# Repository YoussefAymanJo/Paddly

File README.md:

# Paddly
## Description
Paddly is a customized macro pad that combines both customization and functionality. I actually made this to facilitate my daily use. It it consist of 6 switches with multiple functions, an OLED display for soup, customized 2 rotary encoders, and RGB LEDs. I was a beginner in 3D modeling, but I learned a lot from  Fusion tutorials.

## Why it was built
During my day, I use a laptop  almost all day. But while working on projects or designing on Canva, I struggle and tired alot to use multiplekeysy odoly some features, such as  copy manually and undo. So, built a macro pad that provides all the luxury in my usage. As it has 6 MX Cherry switches with customized functions.And 2 rotary encoders and a soup OLED display.

## How to use it / Build it
First, fabricate the PCB and solder the components. After that, set up the firmware on Pico, kmk firmware. Then test each key, OLED, encoders, and LEDs.after that print 
3d models. After that, assemble 3d  enclosure and setup heatinsert and m3 srews. Finally, test everything again.

## Schematic
I made a schematic in KiCad and used Scott Keebs' libraries for the MCU and OLED footprints.

## PCB
I routed the PCB and added the 3d models for components

## CAD
I used Fusion 360 for CAD, and this is my first time in the Fusion world. so i learned frommultiple YouTubee video s. Made a case, a plate, and a top cover. Also signed my name on the cover. I used the encoder's knob and DSA keycaps from the Hackpad Orpheus guide.

## Firmware
I used KMK firmware.

## BOM

## Zine

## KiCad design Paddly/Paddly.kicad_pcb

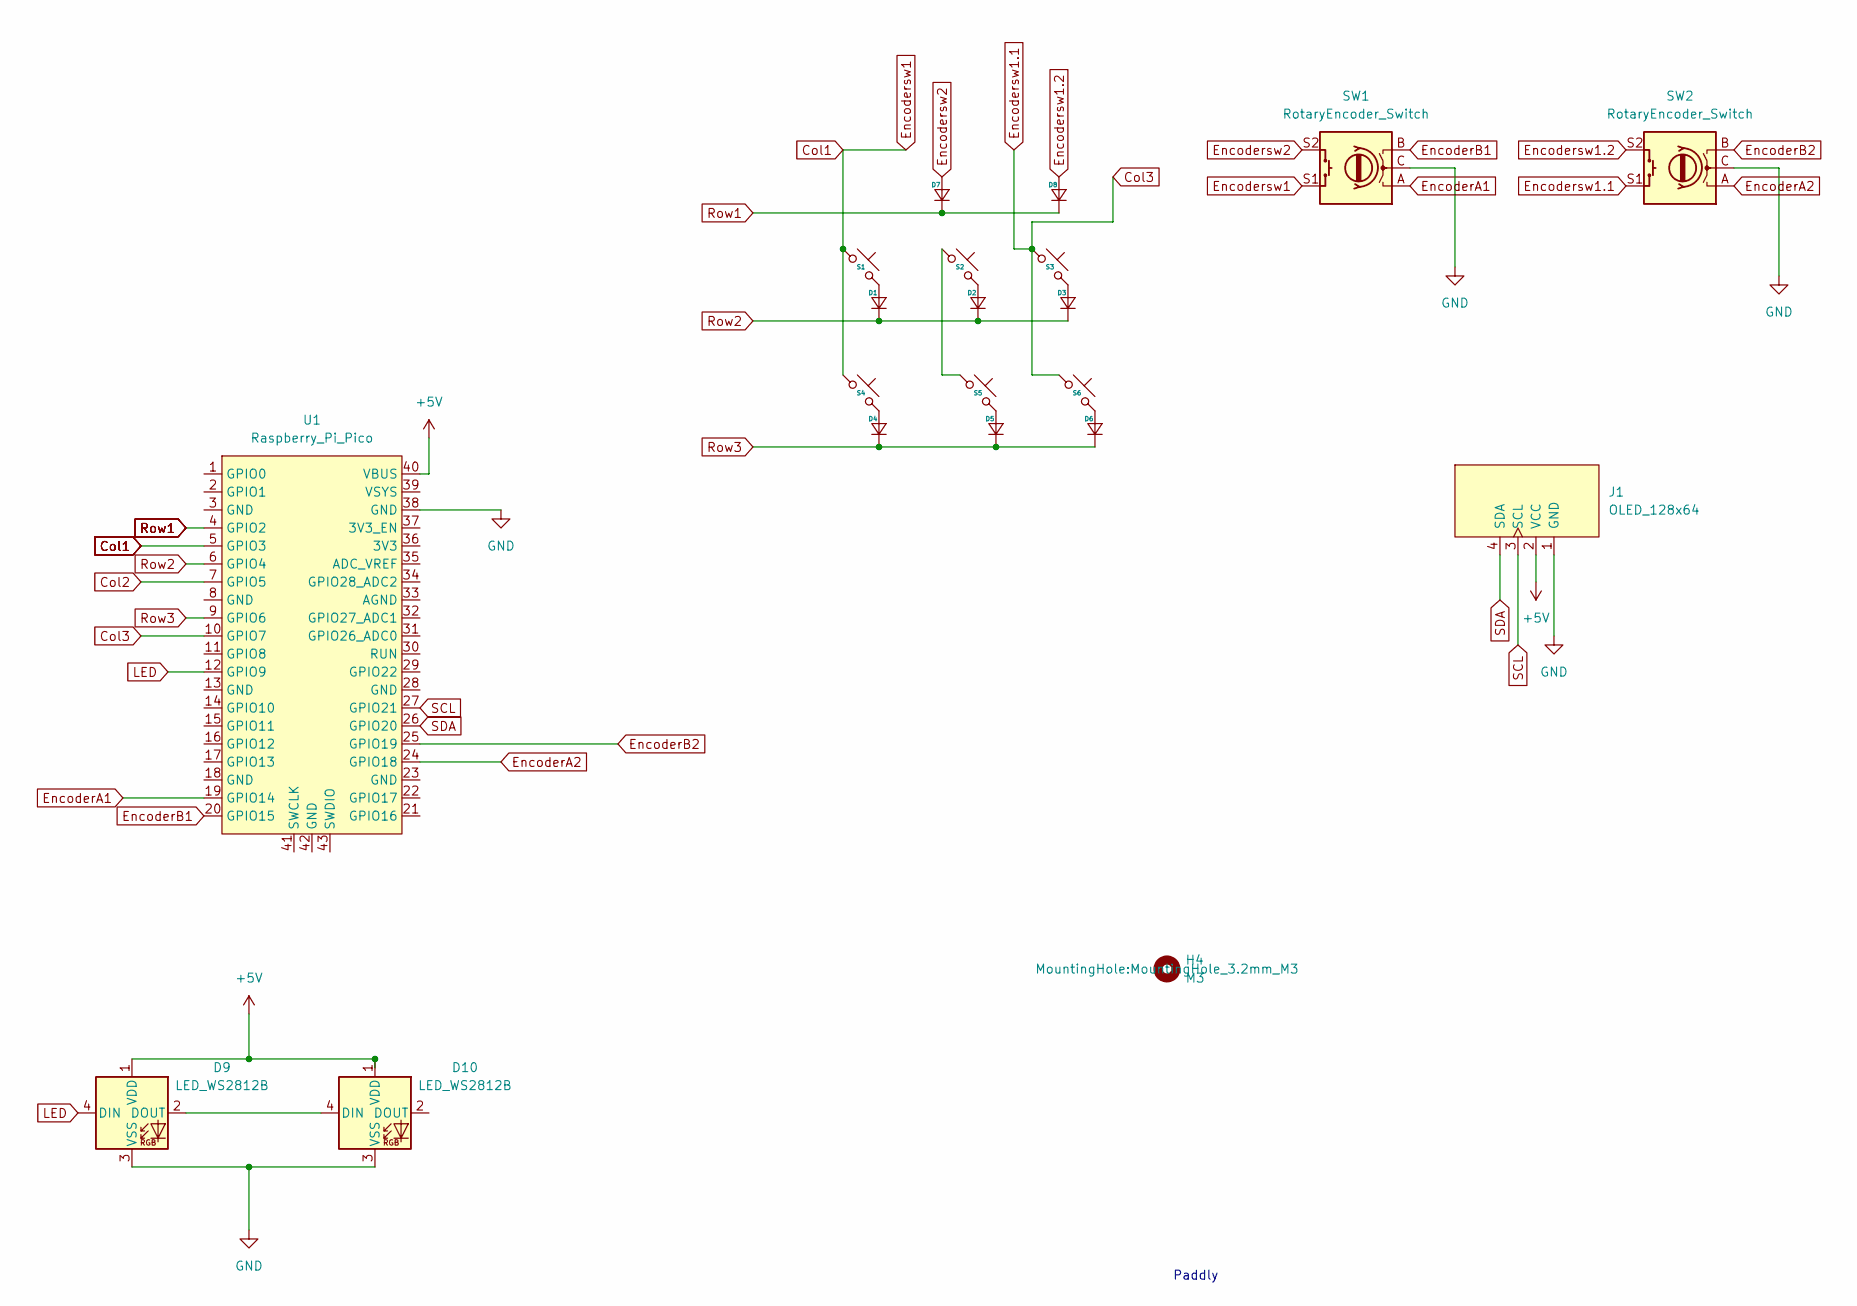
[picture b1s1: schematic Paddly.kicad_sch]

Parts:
D1, D2, D3, D4, D5, D6, D7, D8: Diode_DO-35
D9, D10: LED_WS2812B
H4: M3; MountingHole_3.2mm_M3
J1: OLED_128x64
S1, S2, S3, S4, S5, S6: MX_PCB_1.00u
SW1, SW2: RotaryEncoder_Switch; Encoder_EC11_MX
U1: Raspberry_Pi_Pico

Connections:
+5V: D9.1 (VDD), D10.1 (VDD), J1.2 (VCC), U1.40 (VBUS)
Col1: S1.1, S4.1, SW1.S1, U1.5 (GPIO3)
Col2: U1.7 (GPIO5)
Col3: S3.1, S6.1, SW2.S1, U1.10 (GPIO7)
EncoderA1: SW1.A, U1.19 (GPIO14)
EncoderA2: SW2.A, U1.24 (GPIO18)
EncoderB1: SW1.B, U1.20 (GPIO15)
EncoderB2: SW2.B, U1.25 (GPIO19)
Encodersw1.2: D8.2 (A), SW2.S2
Encodersw2: D7.2 (A), SW1.S2
GND: D9.3 (VSS), D10.3 (VSS), J1.1 (GND), SW1.C, SW2.C, U1.38 (GND)
LED: D9.4 (DIN), U1.12 (GPIO9)
unnamed: D1.2 (A), S1.2
unnamed: D2.2 (A), S2.2
unnamed: D3.2 (A), S3.2
unnamed: D4.2 (A), S4.2
unnamed: D5.2 (A), S5.2
unnamed: D6.2 (A), S6.2
unnamed: D9.2 (DOUT), D10.4 (DIN)
unnamed: S2.1, S5.1
Row1: D7.1 (K), D8.1 (K), U1.4 (GPIO2)
Row2: D1.1 (K), D2.1 (K), D3.1 (K), U1.6 (GPIO4)
Row3: D4.1 (K), D5.1 (K), D6.1 (K), U1.9 (GPIO6)
SCL: J1.3 (SCL), U1.27 (GPIO21)
SDA: J1.4 (SDA), U1.26 (GPIO20)

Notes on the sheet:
Paddly

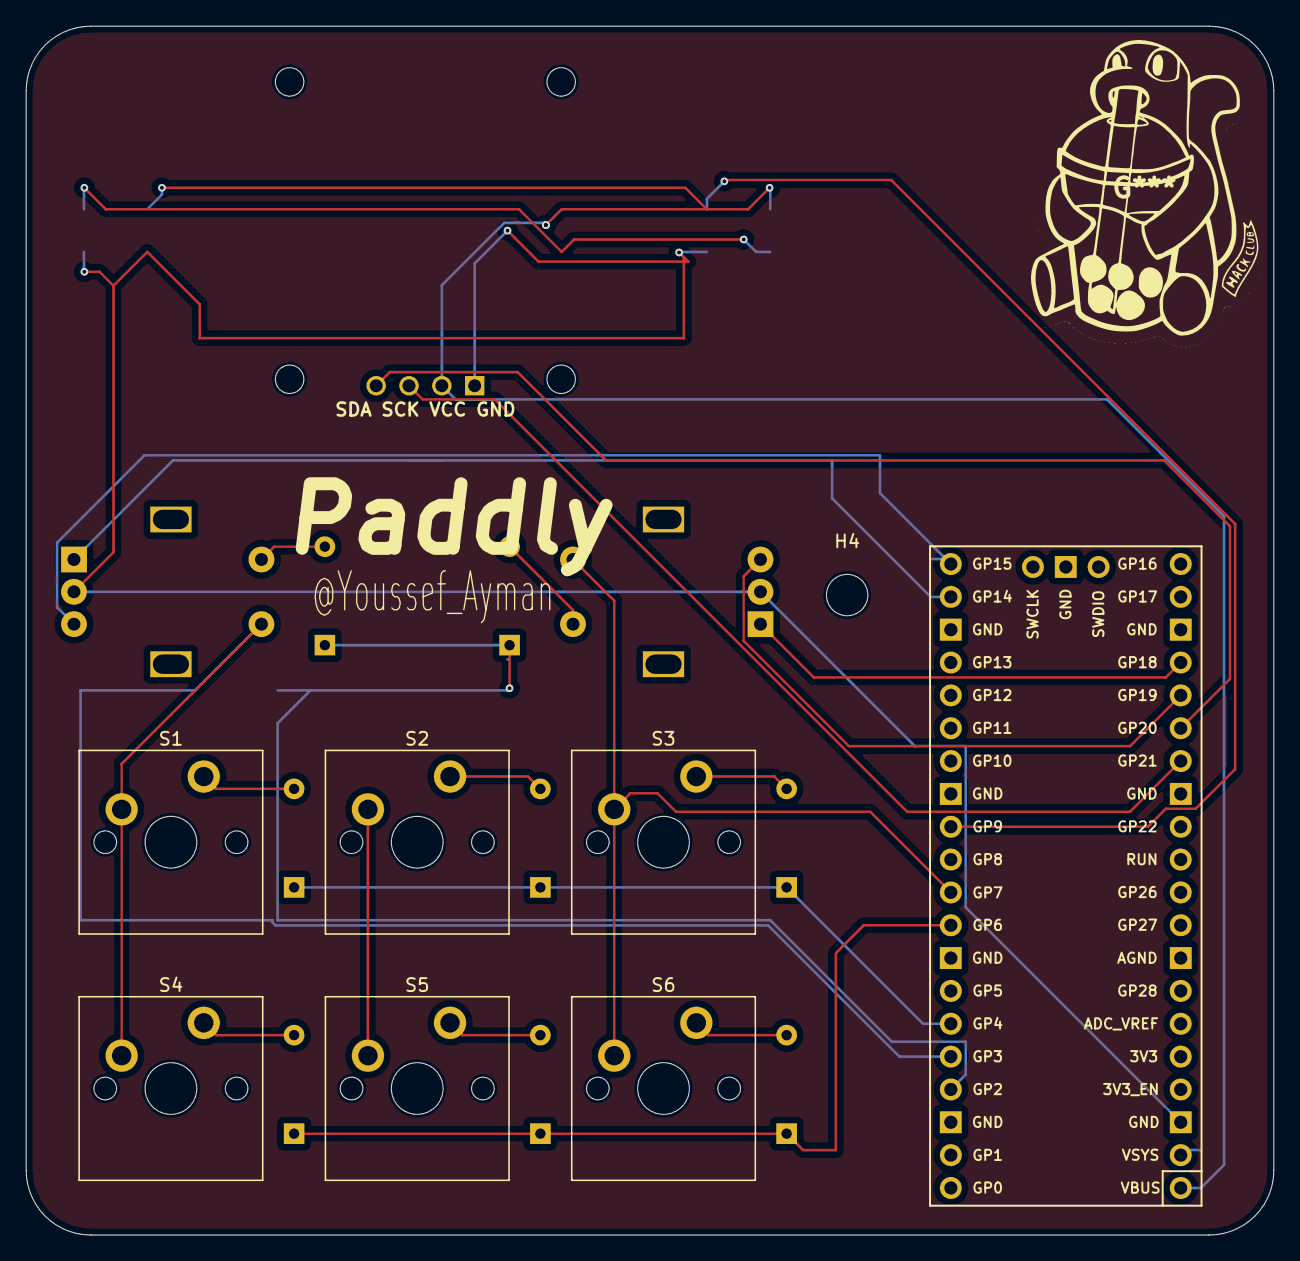
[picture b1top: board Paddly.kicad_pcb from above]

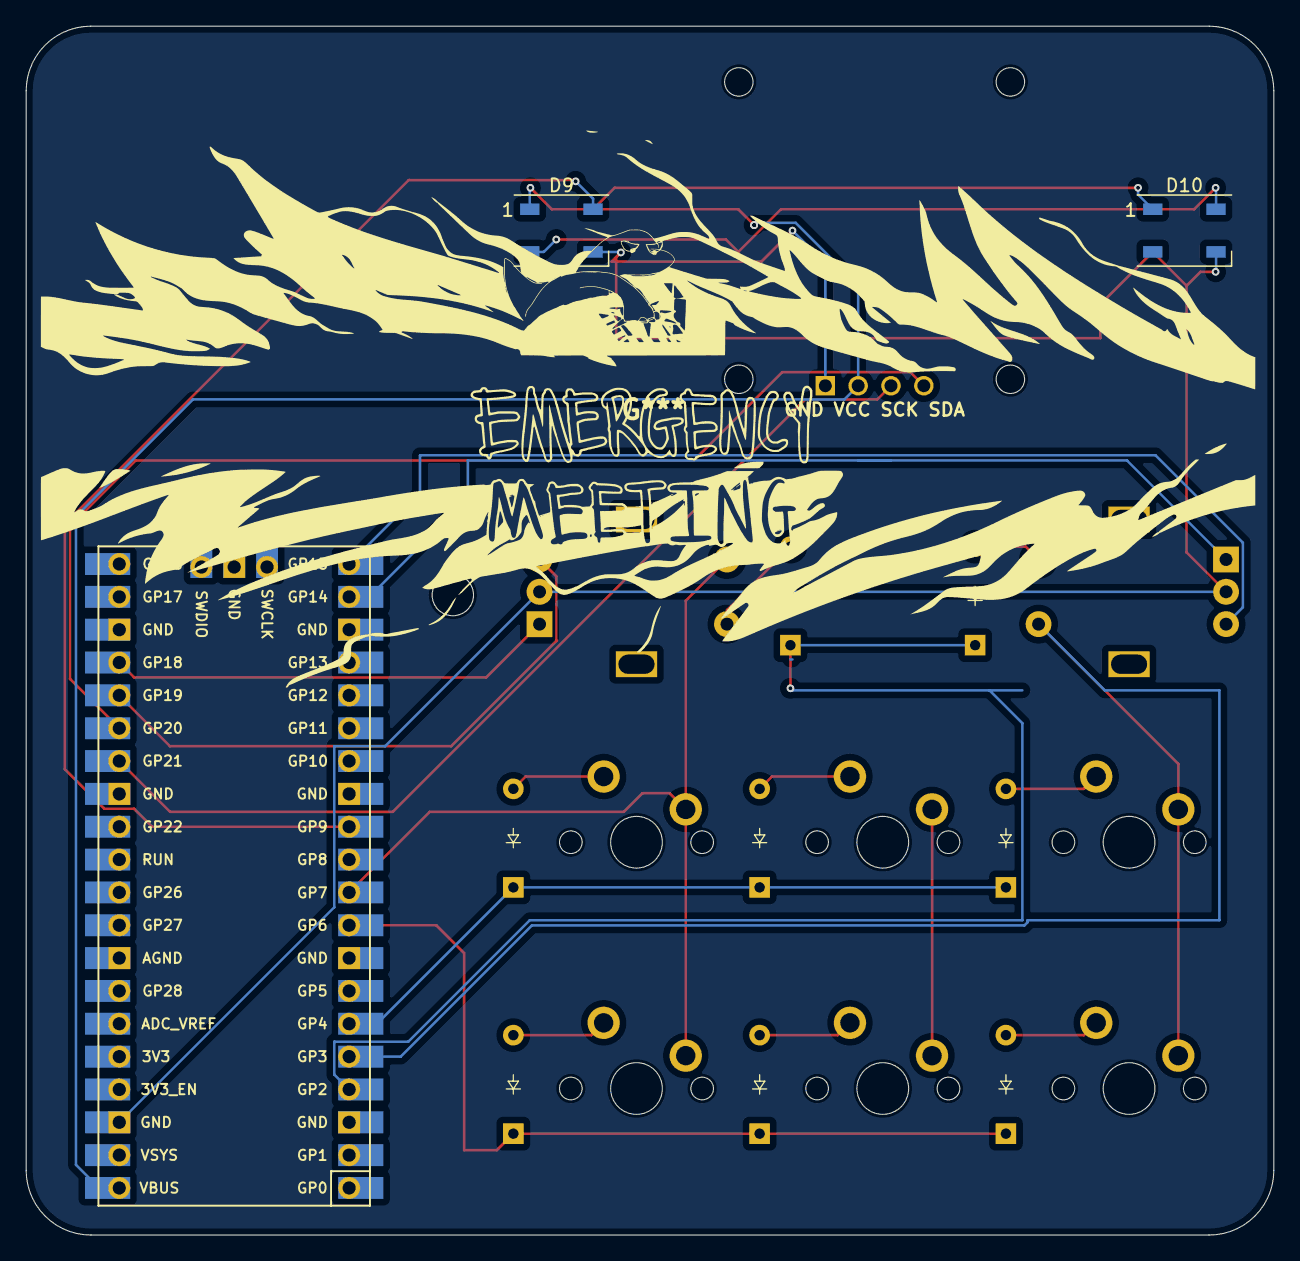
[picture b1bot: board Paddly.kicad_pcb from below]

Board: 2 copper layers, 96.5 x 93.5 mm, 21 parts (11 on the bottom side), 24 nets.

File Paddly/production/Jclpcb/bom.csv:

Designator,Footprint,Quantity,Value,LCSC Part #
"D1, D2, D3, D4, D5, D6, D7, D8",Diode_DO-35,8,~,
"D10, D9",LED_WS2812B,2,LED_WS2812B,
J1,OLED_128x64,1,OLED_128x64,
"S1, S2, S3, S4, S5, S6",MX_PCB_1.00u,6,~,
"SW1, SW2",Encoder_EC11_MX,2,RotaryEncoder_Switch,
U1,Raspberry_Pi_Pico,1,Raspberry_Pi_Pico,

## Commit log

2026-06-10 final
2026-06-10 [ImgBot] Optimize images
    *Total -- 6,554.45kb -> 5,571.54kb (15%)
    /firmware/paddly_kmk_firmware/adafruit-circuitpython-bundle-10.x-mpy-20260606/examples/pixel_framebuf/blinka_16x16.png -- 3.10kb -> 0.53kb (82.98%)
    /images/Screenshot 2026-06-10 184432.png -- 22.15kb -> 9.17kb (58.58%)
    /images/Screenshot 2026-06-10 184440.png -- 39.54kb -> 16.49kb (58.3%)
    /images/Predesign.png -- 24.10kb -> 10.37kb (56.97%)
    /images/Screenshot 2026-06-10 184456.png -- 117.57kb -> 68.56kb (41.69%)
2026-06-11 Rename Zine.pdf to zine.pdf
2026-06-11 Rename Zine.jpg to zine.jpg
2026-06-13 uodate
2026-06-17 updatw
